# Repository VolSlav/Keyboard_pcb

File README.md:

# Keyboard_pcb
librarie utilisé : 
github.com/Biacco42/ProMicroKiCad

github.com/tmk/kicad_lib_tmk

github.com/tmk/keyboard_parts.pretty

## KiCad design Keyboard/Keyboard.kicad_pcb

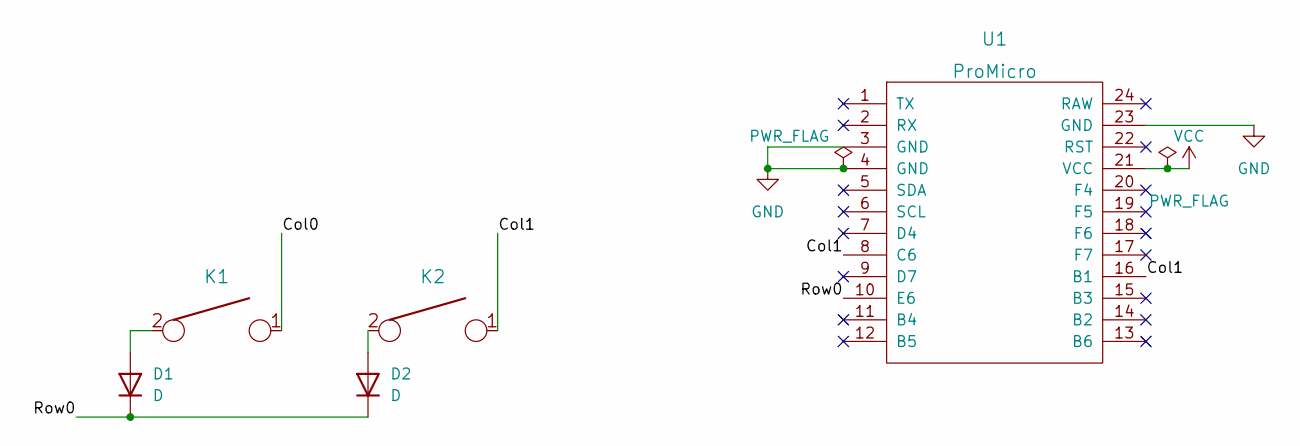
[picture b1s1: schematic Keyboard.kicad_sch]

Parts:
D1, D2: D; D_SOD-123
K1, K2: KEYSW; SW_Cherry_MX_1.00u_PCB
U1: ProMicro

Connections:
/Col0: K1.1
/Col1: K2.1, U1.8 (C6), U1.16 (B1)
/Row0: D1.1 (K), D2.1 (K), U1.10 (E6)
GND: U1.3 (GND), U1.4 (GND), U1.23 (GND)
unnamed: D1.2 (A), K1.2
unnamed: D2.2 (A), K2.2
VCC: U1.21 (VCC)

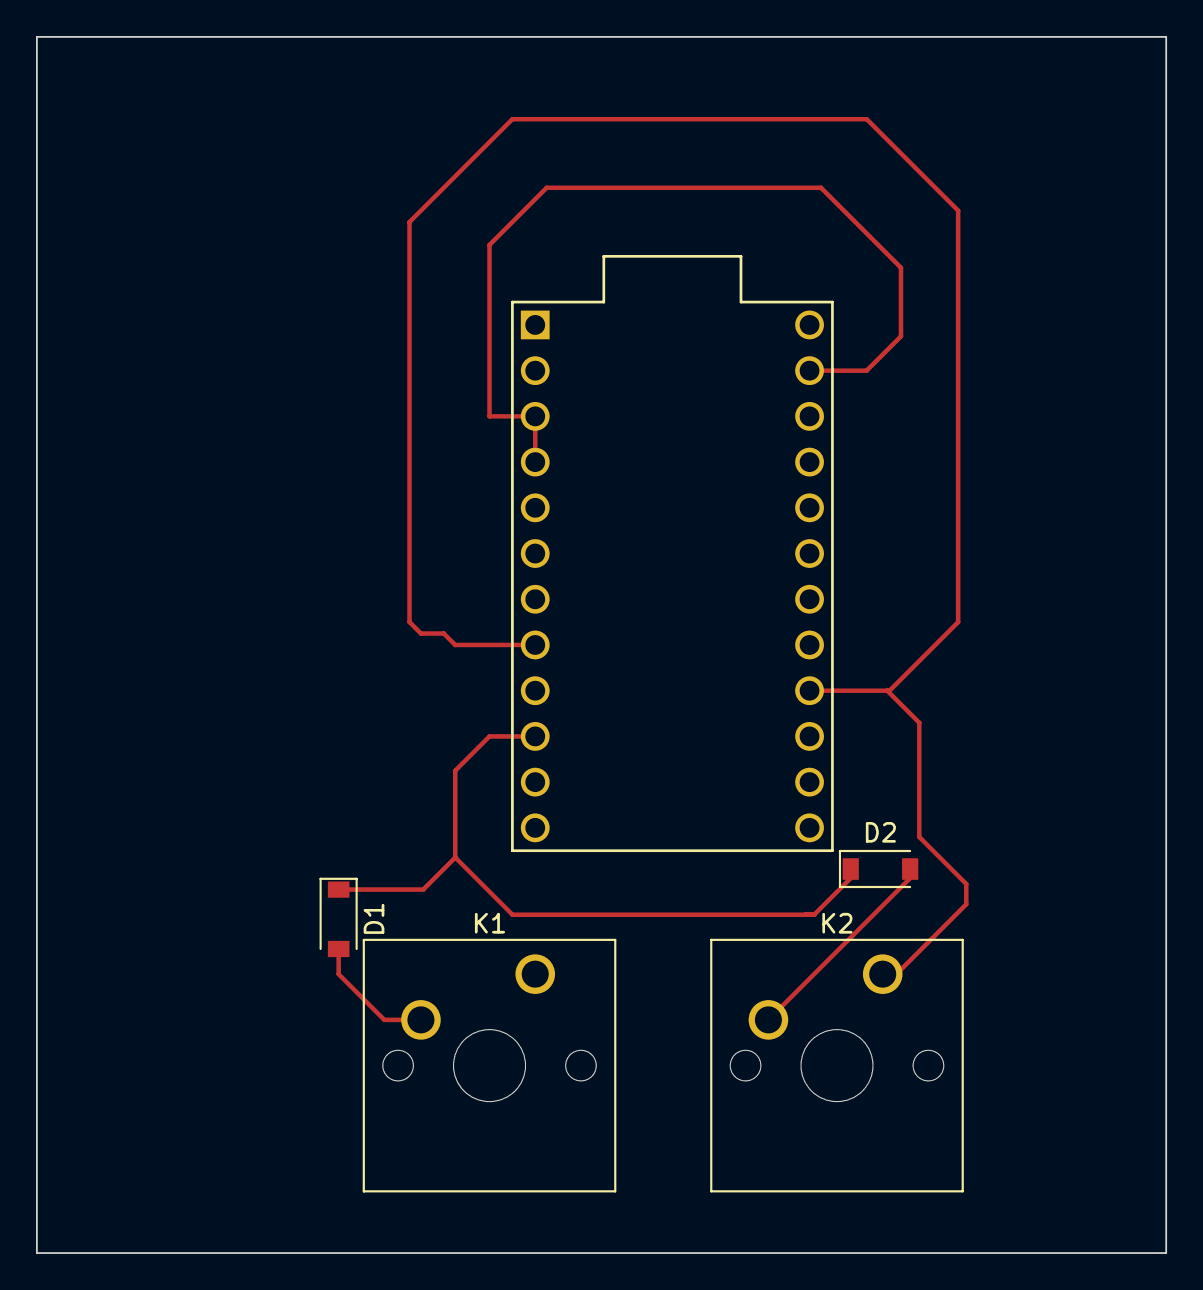
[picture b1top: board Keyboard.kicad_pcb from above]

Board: 2 copper layers, 62.7 x 67.6 mm, 5 parts (0 on the bottom side), 5 nets.
